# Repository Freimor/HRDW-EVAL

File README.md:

## HRDW-EVAL
Bunch of evaluation boards

Design rules for evaluation board:
- Size and pinheader placement defined by breadboard topology
- Silkscreen standart (Name, short description, date format Q1.25)
- Mask color standart (black for final device, white for student's education, red for sensor boards, blue for microcontroller boards, green for other)
- Excessive testpad using, hooks for oscilloscope
- Special via condition (do not use directly on pads. Every signal line through traces)
- Marked resistor only (Except for hard defined)
- All footprints for hand soldering
- Excessive silkscreen marking
- GIT repo address placement required
- All signals on external layers

На русском

- Разрабатываем под установку на макетную плату (так что бы вставала посередине)
- Стандарт маркировки (Наименование, краткий description, дата в формате Q1.25)
- Стандарт по цветам маски (черный под конечное устройство, белый под обучение студентов, красный под сенсор, синий микроконтроллер, зеленый под все остальное)
- Использовать тестпады, зацепы под осциллограф
- Спец условия по расположению via's (не использовать на падах - на удалении. Любой сигнал - через дорожку)
- Резисторы с маркировкой (кроме жестко детерминированных)
- Все посадочные - под ручную пайку
- Развернутая маркировка по возможности
- Указание репозитория на печатной плате
- Все сигналы - на внешних слоях

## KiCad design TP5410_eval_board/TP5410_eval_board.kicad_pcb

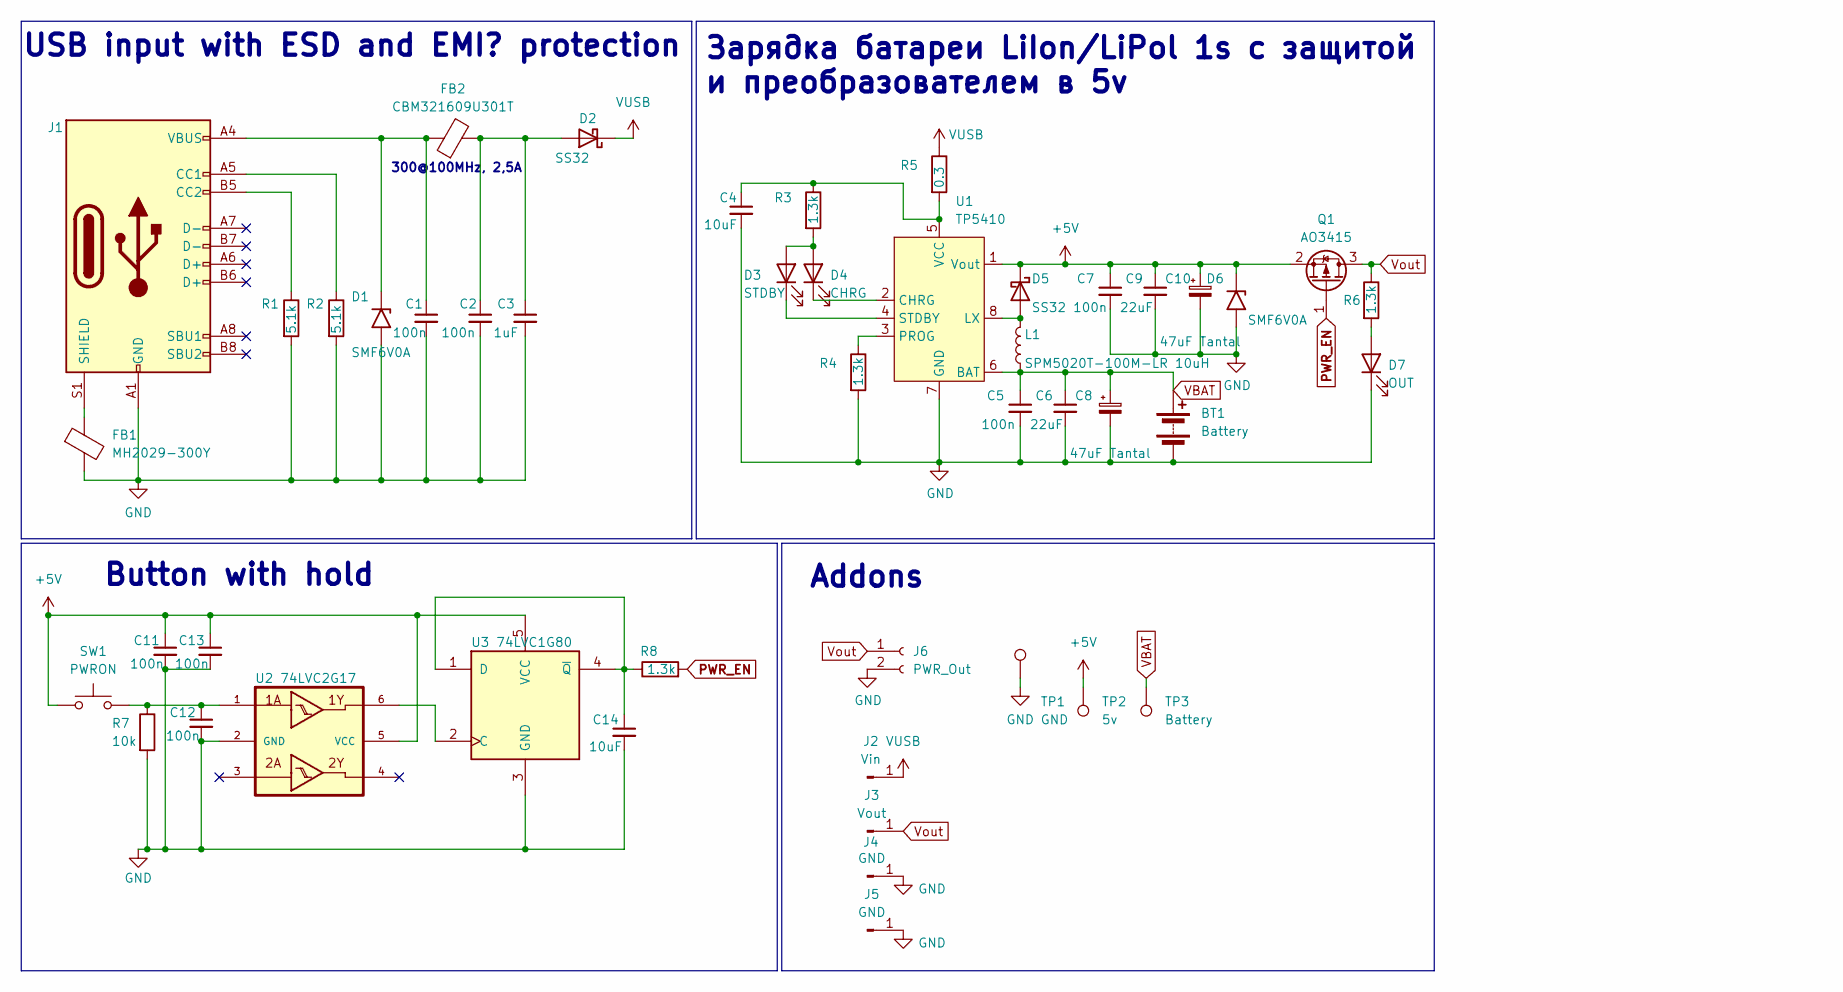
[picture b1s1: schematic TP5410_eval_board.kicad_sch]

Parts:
BT1: Battery; Conn_XH_JSTlike_2pin_X8821WRS-02-9TSN
C1, C2, C5, C7, C11, C12, C13: 100n; C_0402_1005Metric_Pad0.74x0.62mm_HandSolder
C3: 1uF; C_0603_1608Metric_Pad1.08x0.95mm_HandSolder
C4: 10uF; C_0603_1608Metric_Pad1.08x0.95mm_HandSolder
C6, C9: 22uF; C_0805_2012Metric_Pad1.18x1.45mm_HandSolder
C8, C10: 47uF Tantal; CP_EIA-7343-31_Kemet-D
C14: 10uF; C_0603_1608Metric
D1, D6: SMF6V0A; D_SOD-123F
D2, D5: SS32; D_SMA-SMB_Universal_Handsoldering
D3: STDBY; LED_0603_1608Metric_Pad1.05x0.95mm_HandSolder
D4: CHRG; LED_0603_1608Metric_Pad1.05x0.95mm_HandSolder
D7: OUT; LED_0603_1608Metric_Pad1.05x0.95mm_HandSolder
FB1: MH2029-300Y; L_0805_2012Metric_Pad1.05x1.20mm_HandSolder
FB2: CBM321609U301T; L_1206_3216Metric_Pad1.22x1.90mm_HandSolder
J1: USB_C_Receptacle_USB2.0; RUICHI_TYPE-C-16PF-020
J2: Vin; Castellated_hole_2.54
J3: Vout; Castellated_hole_2.54
J4, J5: GND; Castellated_hole_2.54
J6: PWR_Out; Conn_XH_JSTlike_2pin_X8821WRS-02-9TSN
L1: SPM5020T-100M-LR 10uH; INDUCTOR_SPM5020T
Q1: AO3415; SOT-23
R1, R2: 5.1k; R_0402_1005Metric_Pad0.72x0.64mm_HandSolder
R3, R4, R6, R8: 1.3k; R_0603_1608Metric_Pad0.98x0.95mm_HandSolder
R5: 0.3; R_1210_3225Metric_Pad1.30x2.65mm_HandSolder
R7: 10k; R_0402_1005Metric_Pad0.72x0.64mm_HandSolder
SW1: PWRON; SW_SMD_PAN_EVPAS
TP1: GND; Test_Ring_TH
TP2: 5v; Test_Ring_TH
TP3: Battery; Test_Ring_TH
U1: TP5410
U2: 74LVC2G17; SOT-23-6_Handsoldering
U3: 74LVC1G80

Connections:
+5V: C7.1, C9.1, C10.1, C11.1, C13.1, D5.1 (K), D6.1 (A1), Q1.2 (S), SW1.1, TP2.1, U1.1 (Vout), U2.5 (VCC), U3.5 (VCC)
GND: BT1.2 (-), BT1.S, C1.2, C2.2, C3.2, C4.2, C5.2, C6.2, C7.2, C8.2, C9.2, C10.2, C11.2, C12.2, C13.2, C14.2, D1.2 (A2), D6.2 (A2), D7.1 (K), FB1.2, J1.A1 (GND), J1.A12 (GND), J1.B1 (GND), J1.B12 (GND), J4.1, J5.1, J6.2, J6.S, R1.2, R2.2, R4.2, R7.2, TP1.1, U1.7 (GND), U1.9, U2.2 (GND), U3.3 (GND)
unnamed: C12.1, R7.1, SW1.2, U2.1
unnamed: C1.1, D1.1 (A1), FB2.1, J1.A4 (VBUS), J1.A9 (VBUS), J1.B4 (VBUS), J1.B9 (VBUS)
unnamed: C2.1, C3.1, D2.2 (A), FB2.2
unnamed: D3.2 (A), D4.2 (A), R3.2
unnamed: D3.1 (K), U1.4 (STDBY)
unnamed: D4.1 (K), U1.2 (CHRG)
unnamed: D5.2 (A), L1.2, U1.8 (LX)
unnamed: D7.2 (A), R6.2
unnamed: J1.A5 (CC1), R2.1
unnamed: J1.B5 (CC2), R1.1
unnamed: FB1.1, J1.S1 (SHIELD)
unnamed: R4.1, U1.3 (PROG)
unnamed: C4.1, R3.1, R5.2, U1.5 (VCC)
unnamed: U2.6, U3.2 (C)
unnamed: C14.1, R8.1, U3.1 (D), U3.4 (~Q)
PWR_EN: Q1.1 (G), R8.2
VBAT: BT1.1 (+), C5.1, C6.1, C8.1, L1.1, TP3.1, U1.6 (BAT)
VUSB: D2.1 (K), J2.1, R5.1
Vout: J3.1, J6.1, Q1.3 (D), R6.1

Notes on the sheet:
Зарядка батареи LiIon/LiPol 1s с защитой и преобразователем в 5v
300@100MHz, 2,5A
USB input with ESD and EMI? protection
Button with hold
Addons

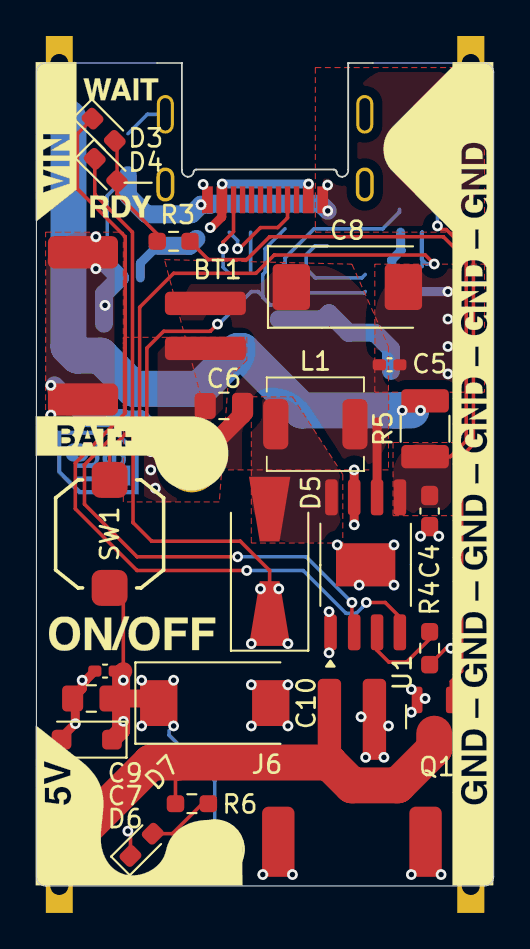
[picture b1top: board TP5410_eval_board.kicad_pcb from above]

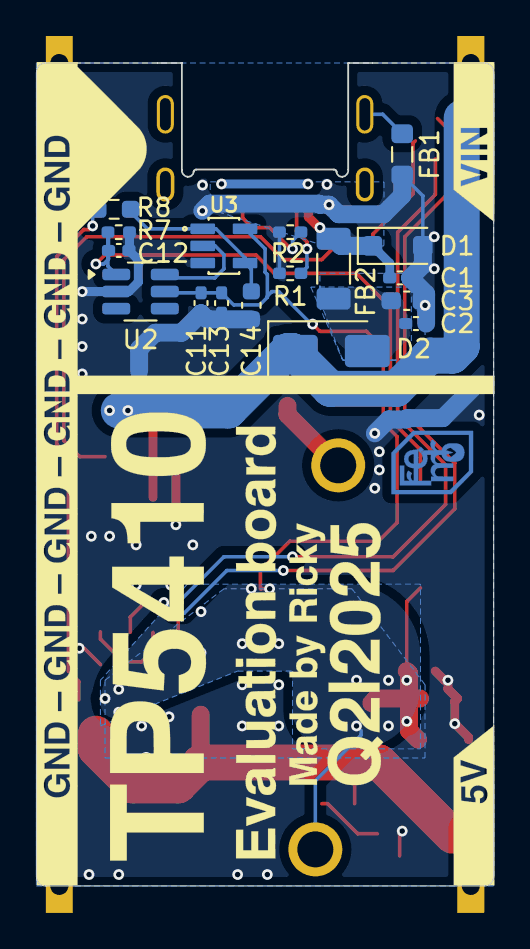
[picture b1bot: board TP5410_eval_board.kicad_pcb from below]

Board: 2 copper layers, 25.4 x 45.7 mm, 48 parts (17 on the bottom side), 21 nets.

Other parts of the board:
Ref**: Val**; graphic
